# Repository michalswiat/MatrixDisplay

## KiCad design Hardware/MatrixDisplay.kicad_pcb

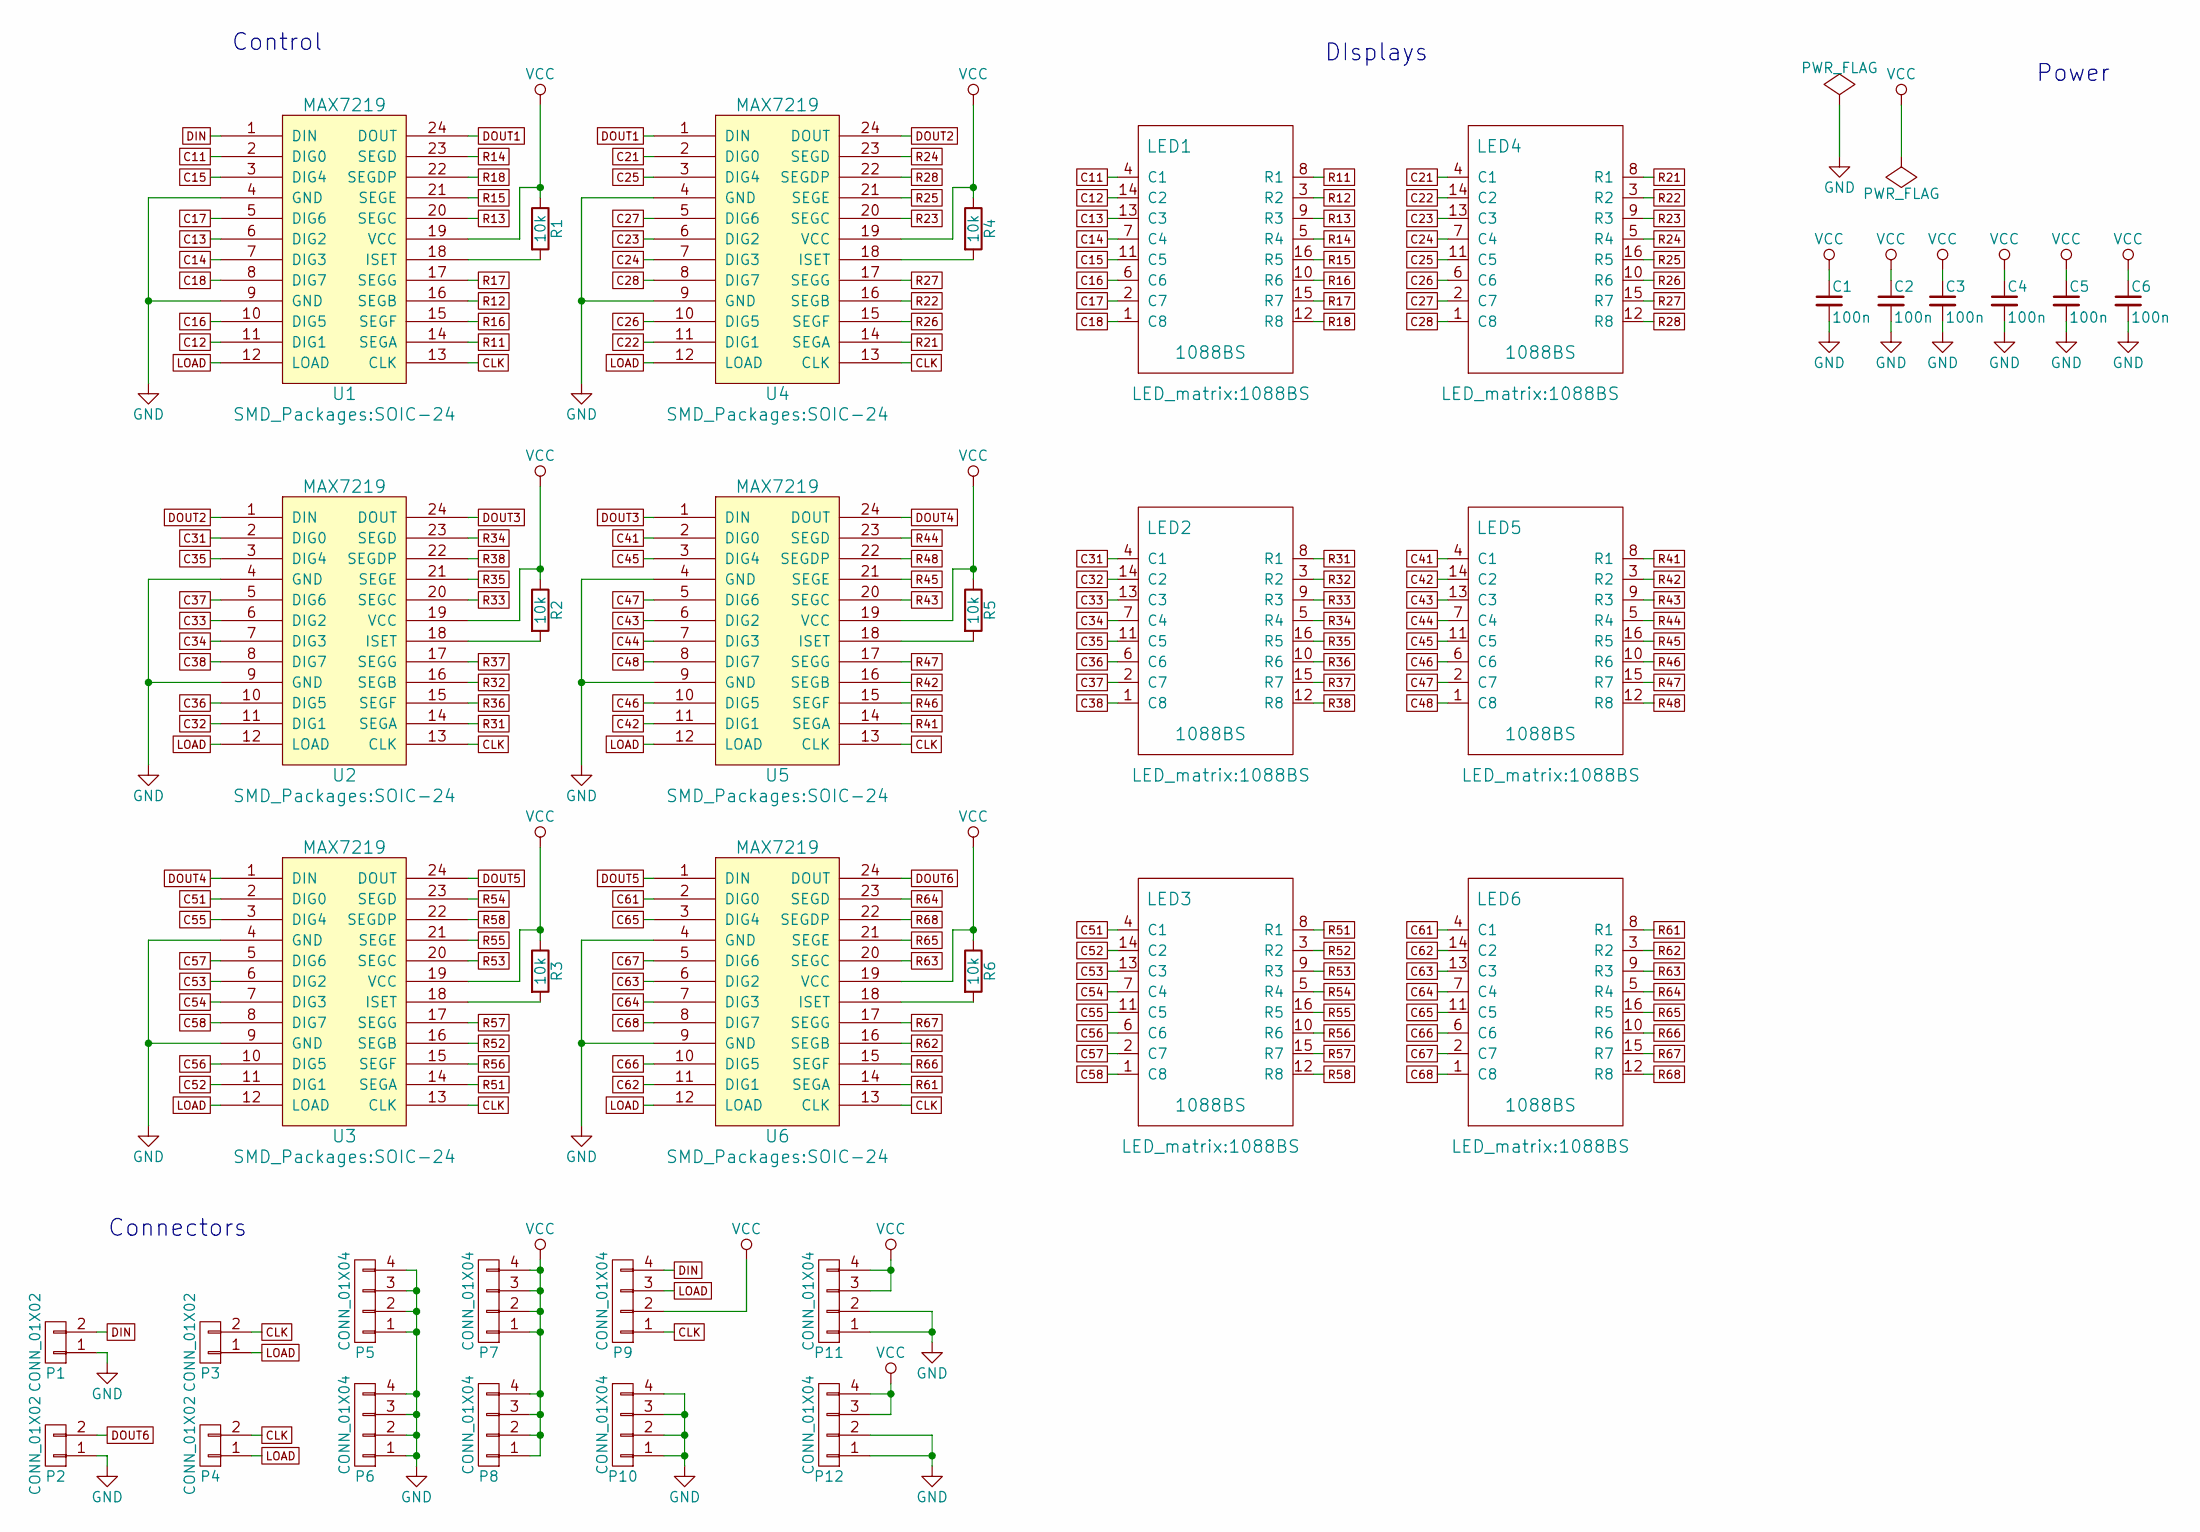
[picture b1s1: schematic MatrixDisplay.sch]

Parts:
C1, C2, C3, C4, C5, C6: 100n; C_0603_HandSoldering
LED1, LED2, LED3, LED4, LED5, LED6: 1088BS
P1, P2, P3, P4: CONN_01X02; socket_strip_smd_1x02
P5, P6, P7, P8: CONN_01X04; socket_strip_smd_1x04
P9, P10, P11, P12: CONN_01X04; Socket_Strip_Straight_1x04
R1, R2, R3, R4, R5, R6: 10k; R_0603_HandSoldering
U1, U2, U3, U4, U5, U6: MAX7219; SOIC-24

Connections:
C11: LED1.4 (C1), U1.2 (DIG0)
C12: LED1.14 (C2), U1.11 (DIG1)
C13: LED1.13 (C3), U1.6 (DIG2)
C14: LED1.7 (C4), U1.7 (DIG3)
C15: LED1.11 (C5), U1.3 (DIG4)
C16: LED1.6 (C6), U1.10 (DIG5)
C17: LED1.2 (C7), U1.5 (DIG6)
C18: LED1.1 (C8), U1.8 (DIG7)
C21: LED4.4 (C1), U4.2 (DIG0)
C22: LED4.14 (C2), U4.11 (DIG1)
C23: LED4.13 (C3), U4.6 (DIG2)
C24: LED4.7 (C4), U4.7 (DIG3)
C25: LED4.11 (C5), U4.3 (DIG4)
C26: LED4.6 (C6), U4.10 (DIG5)
C27: LED4.2 (C7), U4.5 (DIG6)
C28: LED4.1 (C8), U4.8 (DIG7)
C31: LED2.4 (C1), U2.2 (DIG0)
C32: LED2.14 (C2), U2.11 (DIG1)
C33: LED2.13 (C3), U2.6 (DIG2)
C34: LED2.7 (C4), U2.7 (DIG3)
C35: LED2.11 (C5), U2.3 (DIG4)
C36: LED2.6 (C6), U2.10 (DIG5)
C37: LED2.2 (C7), U2.5 (DIG6)
C38: LED2.1 (C8), U2.8 (DIG7)
C41: LED5.4 (C1), U5.2 (DIG0)
C42: LED5.14 (C2), U5.11 (DIG1)
C43: LED5.13 (C3), U5.6 (DIG2)
C44: LED5.7 (C4), U5.7 (DIG3)
C45: LED5.11 (C5), U5.3 (DIG4)
C46: LED5.6 (C6), U5.10 (DIG5)
C47: LED5.2 (C7), U5.5 (DIG6)
C48: LED5.1 (C8), U5.8 (DIG7)
C51: LED3.4 (C1), U3.2 (DIG0)
C52: LED3.14 (C2), U3.11 (DIG1)
C53: LED3.13 (C3), U3.6 (DIG2)
C54: LED3.7 (C4), U3.7 (DIG3)
C55: LED3.11 (C5), U3.3 (DIG4)
C56: LED3.6 (C6), U3.10 (DIG5)
C57: LED3.2 (C7), U3.5 (DIG6)
C58: LED3.1 (C8), U3.8 (DIG7)
C61: LED6.4 (C1), U6.2 (DIG0)
C62: LED6.14 (C2), U6.11 (DIG1)
C63: LED6.13 (C3), U6.6 (DIG2)
C64: LED6.7 (C4), U6.7 (DIG3)
C65: LED6.11 (C5), U6.3 (DIG4)
C66: LED6.6 (C6), U6.10 (DIG5)
C67: LED6.2 (C7), U6.5 (DIG6)
C68: LED6.1 (C8), U6.8 (DIG7)
CLK: P3.2, P4.2, P9.1, U1.13 (CLK), U2.13 (CLK), U3.13 (CLK), U4.13 (CLK), U5.13 (CLK), U6.13 (CLK)
DIN: P1.2, P9.4, U1.1 (DIN)
DOUT1: U1.24 (DOUT), U4.1 (DIN)
DOUT2: U2.1 (DIN), U4.24 (DOUT)
DOUT3: U2.24 (DOUT), U5.1 (DIN)
DOUT4: U3.1 (DIN), U5.24 (DOUT)
DOUT5: U3.24 (DOUT), U6.1 (DIN)
DOUT6: P2.2, U6.24 (DOUT)
GND: C1.2, C2.2, C3.2, C4.2, C5.2, C6.2, P1.1, P2.1, P5.1, P5.2, P5.3, P5.4, P6.1, P6.2, P6.3, P6.4, P10.1, P10.2, P10.3, P10.4, P11.1, P11.2, P12.1, P12.2, U1.4 (GND), U1.9 (GND), U2.4 (GND), U2.9 (GND), U3.4 (GND), U3.9 (GND), U4.4 (GND), U4.9 (GND), U5.4 (GND), U5.9 (GND), U6.4 (GND), U6.9 (GND)
LOAD: P3.1, P4.1, P9.3, U1.12 (LOAD), U2.12 (LOAD), U3.12 (LOAD), U4.12 (LOAD), U5.12 (LOAD), U6.12 (LOAD)
unnamed: R1.2, U1.18 (ISET)
unnamed: R2.2, U2.18 (ISET)
unnamed: R3.2, U3.18 (ISET)
unnamed: R4.2, U4.18 (ISET)
unnamed: R5.2, U5.18 (ISET)
unnamed: R6.2, U6.18 (ISET)
R11: LED1.8 (R1), U1.14 (SEGA)
R12: LED1.3 (R2), U1.16 (SEGB)
R13: LED1.9 (R3), U1.20 (SEGC)
R14: LED1.5 (R4), U1.23 (SEGD)
R15: LED1.16 (R5), U1.21 (SEGE)
R16: LED1.10 (R6), U1.15 (SEGF)
R17: LED1.15 (R7), U1.17 (SEGG)
R18: LED1.12 (R8), U1.22 (SEGDP)
R21: LED4.8 (R1), U4.14 (SEGA)
R22: LED4.3 (R2), U4.16 (SEGB)
R23: LED4.9 (R3), U4.20 (SEGC)
R24: LED4.5 (R4), U4.23 (SEGD)
R25: LED4.16 (R5), U4.21 (SEGE)
R26: LED4.10 (R6), U4.15 (SEGF)
R27: LED4.15 (R7), U4.17 (SEGG)
R28: LED4.12 (R8), U4.22 (SEGDP)
R31: LED2.8 (R1), U2.14 (SEGA)
R32: LED2.3 (R2), U2.16 (SEGB)
R33: LED2.9 (R3), U2.20 (SEGC)
R34: LED2.5 (R4), U2.23 (SEGD)
R35: LED2.16 (R5), U2.21 (SEGE)
R36: LED2.10 (R6), U2.15 (SEGF)
R37: LED2.15 (R7), U2.17 (SEGG)
R38: LED2.12 (R8), U2.22 (SEGDP)
R41: LED5.8 (R1), U5.14 (SEGA)
R42: LED5.3 (R2), U5.16 (SEGB)
R43: LED5.9 (R3), U5.20 (SEGC)
R44: LED5.5 (R4), U5.23 (SEGD)
R45: LED5.16 (R5), U5.21 (SEGE)
R46: LED5.10 (R6), U5.15 (SEGF)
R47: LED5.15 (R7), U5.17 (SEGG)
R48: LED5.12 (R8), U5.22 (SEGDP)
R51: LED3.8 (R1), U3.14 (SEGA)
R52: LED3.3 (R2), U3.16 (SEGB)
R53: LED3.9 (R3), U3.20 (SEGC)
R54: LED3.5 (R4), U3.23 (SEGD)
R55: LED3.16 (R5), U3.21 (SEGE)
R56: LED3.10 (R6), U3.15 (SEGF)
R57: LED3.15 (R7), U3.17 (SEGG)
R58: LED3.12 (R8), U3.22 (SEGDP)
R61: LED6.8 (R1), U6.14 (SEGA)
R62: LED6.3 (R2), U6.16 (SEGB)
R63: LED6.9 (R3), U6.20 (SEGC)
R64: LED6.5 (R4), U6.23 (SEGD)
R65: LED6.16 (R5), U6.21 (SEGE)
R66: LED6.10 (R6), U6.15 (SEGF)
R67: LED6.15 (R7), U6.17 (SEGG)
R68: LED6.12 (R8), U6.22 (SEGDP)
VCC: C1.1, C2.1, C3.1, C4.1, C5.1, C6.1, P7.1, P7.2, P7.3, P7.4, P8.1, P8.2, P8.3, P8.4, P9.2, P11.3, P11.4, P12.3, P12.4, R1.1, R2.1, R3.1, R4.1, R5.1, R6.1, U1.19 (VCC), U2.19 (VCC), U3.19 (VCC), U4.19 (VCC), U5.19 (VCC), U6.19 (VCC)

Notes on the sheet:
DIsplays
Control
Connectors
Power

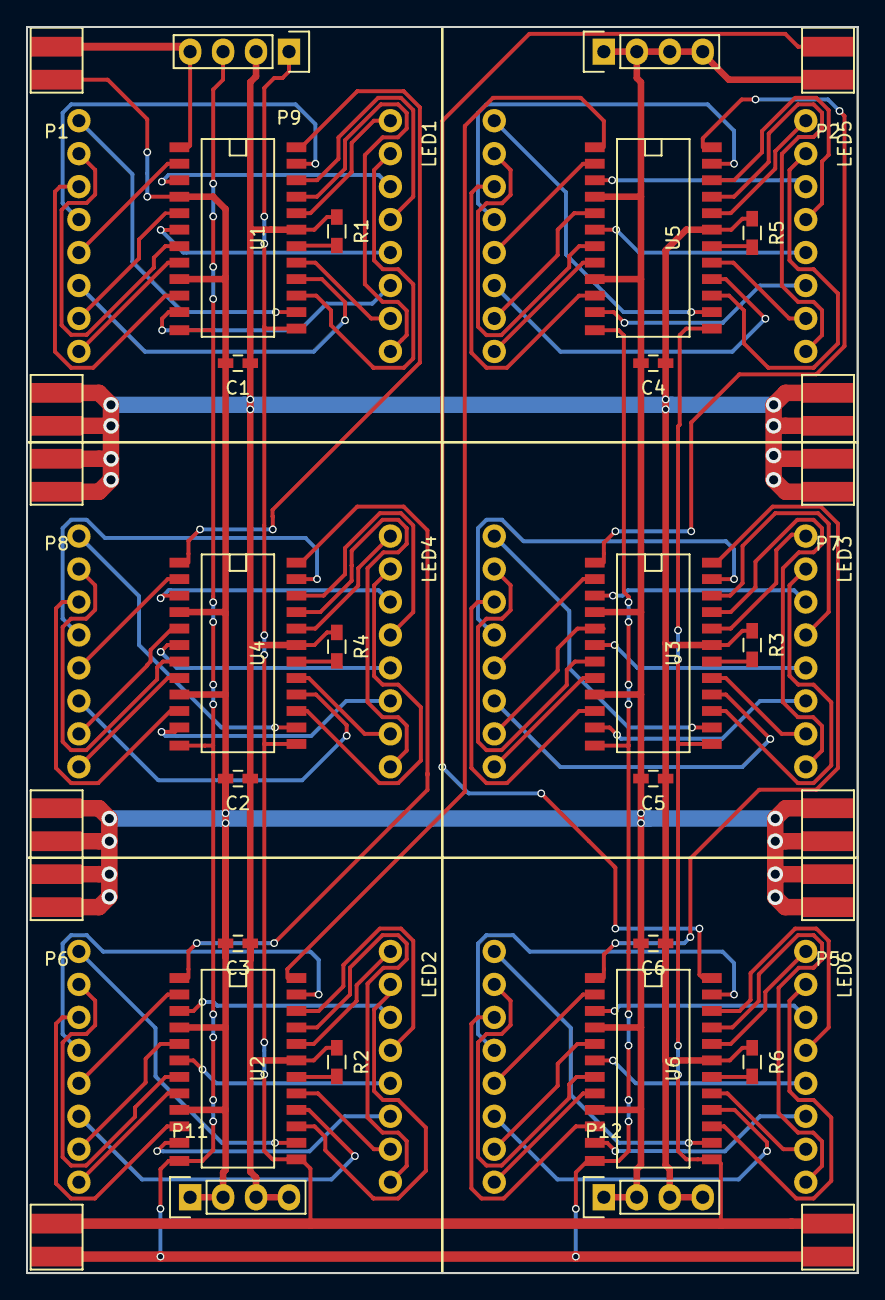
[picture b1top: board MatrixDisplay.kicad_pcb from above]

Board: 2 copper layers, 64.0 x 96.0 mm, 36 parts (0 on the bottom side), 113 nets.

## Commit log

2016-07-31 Initial hardware info
2016-07-31 Initila software info
2016-07-31 Add Kicad project file
2016-07-31 Add MAX7219 to schematic
2016-08-06 Create PCB and schematic
2016-08-08 Gnerate gerber file
2016-08-26 Change SOIC-24 package
